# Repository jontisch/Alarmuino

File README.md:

# Alarmuino
Much wow, very alarm, such security

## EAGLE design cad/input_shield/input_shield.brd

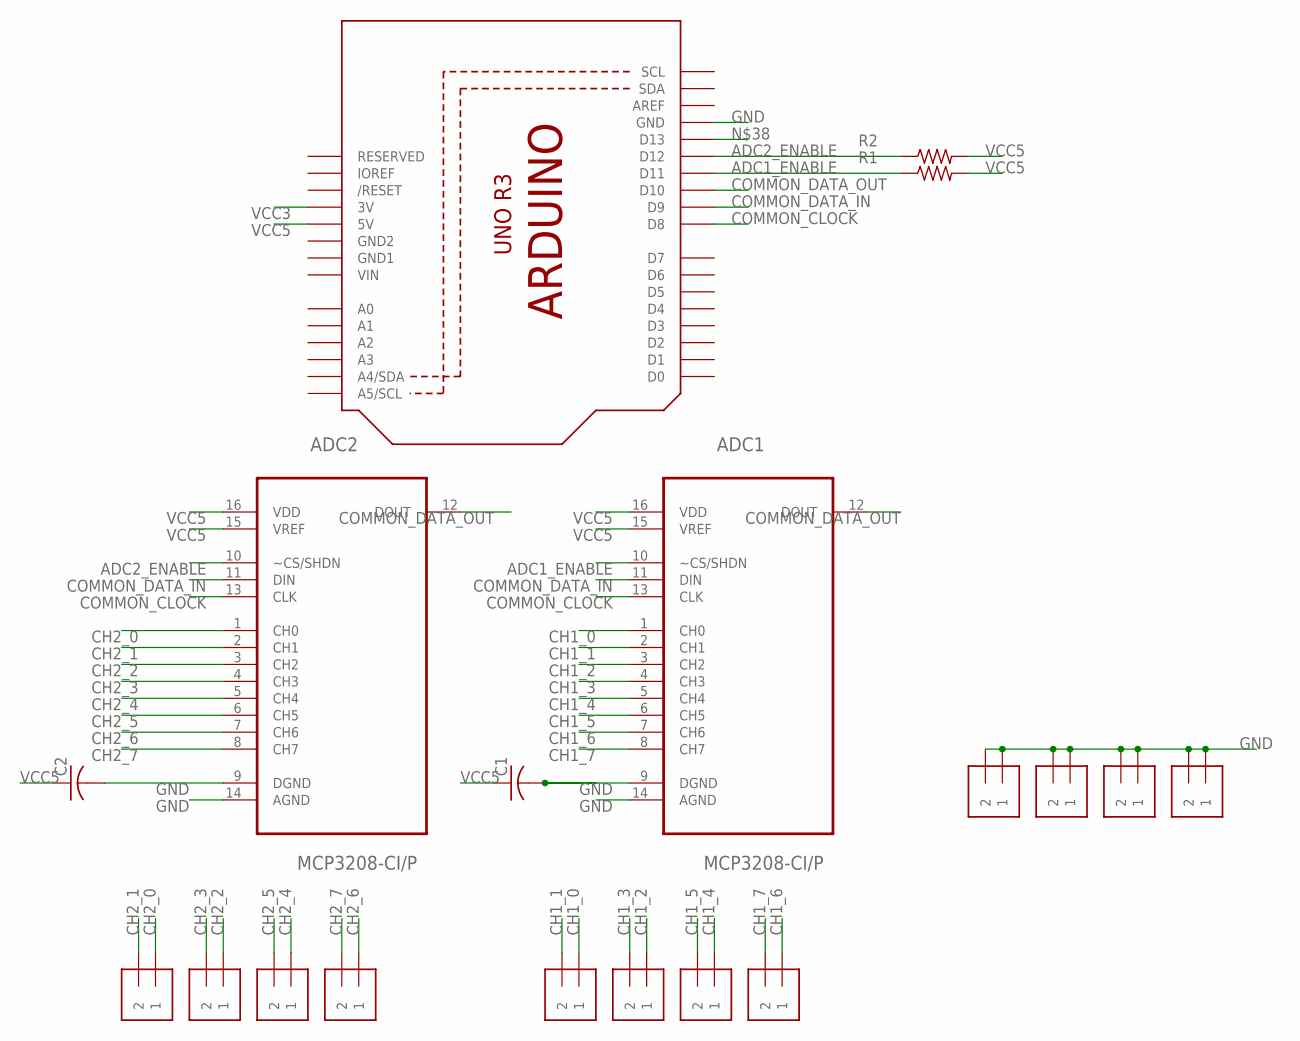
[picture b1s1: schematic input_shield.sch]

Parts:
ADC1, ADC2: MCP3208-CI/P; DIP254P762X432-16
C1, C2: C-US025-025X050; C025-025X050
J1, J2, J3, J4, J5, J6, J7, J8, J9, J10, J11, J12: 1X2-3.5MM
R1, R2: R-US_0204/5; 0204/5
U1: ARDUINOR3-DIMENSION; ARDUINOR3

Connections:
ADC1_ENABLE: ADC1.10 (~CS/SHDN), R1.1, U1.D11
ADC2_ENABLE: ADC2.10 (~CS/SHDN), R2.1, U1.D12
CH1_0: ADC1.1 (CH0), J5.1
CH1_1: ADC1.2 (CH1), J5.2
CH1_2: ADC1.3 (CH2), J6.1
CH1_3: ADC1.4 (CH3), J6.2
CH1_4: ADC1.5 (CH4), J7.1
CH1_5: ADC1.6 (CH5), J7.2
CH1_6: ADC1.7 (CH6), J8.1
CH1_7: ADC1.8 (CH7), J8.2
CH2_0: ADC2.1 (CH0), J1.1
CH2_1: ADC2.2 (CH1), J1.2
CH2_2: ADC2.3 (CH2), J2.1
CH2_3: ADC2.4 (CH3), J2.2
CH2_4: ADC2.5 (CH4), J3.1
CH2_5: ADC2.6 (CH5), J3.2
CH2_6: ADC2.7 (CH6), J4.1
CH2_7: ADC2.8 (CH7), J4.2
COMMON_CLOCK: ADC1.13 (CLK), ADC2.13 (CLK), U1.D8
COMMON_DATA_IN: ADC1.11 (DIN), ADC2.11 (DIN), U1.D9
COMMON_DATA_OUT: ADC1.12 (DOUT), ADC2.12 (DOUT), U1.D10
GND: ADC1.9 (DGND), ADC1.14 (AGND), ADC2.9 (DGND), ADC2.14 (AGND), C1.2, C2.2, J9.1, J9.2, J10.1, J10.2, J11.1, J11.2, J12.1, J12.2, U1.GND
GND1: U1.GND1
GND2: U1.GND2
VCC3: U1.3V
VCC5: ADC1.15 (VREF), ADC1.16 (VDD), ADC2.15 (VREF), ADC2.16 (VDD), C1.1, C2.1, R1.2, R2.2, U1.5V
VIN: U1.VIN

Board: 2 copper layers, 19 parts (0 on the bottom side), 23 nets, no tracks yet.

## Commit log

2017-08-25 folder structure
2017-08-30 Some docs and libs
2017-08-31 Some eagle schematics for an input shield
2017-09-01 First steps on a class for the ADC sampler
2017-09-02 More arduino stuff
